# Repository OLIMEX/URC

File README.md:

# URC
Universal Remote Control soldering kit

How to transfer a command from a remote control to the Olimex URC module:

1. Enter learning mode - press and hold both buttons until red LED turns on, then release both buttons;
2. Assing a button for the new comamnd - press button 1 or button 2 until LED blinks few times then release the button; the red LED remains on;
3. Programming - point the front of the Olimex URC module to the remote control; then press and hold the command you wish to store until the red LED turns off.

## License
* License for the software is GPL3
* License for the hardware is CERN OHL v1.2
* License for the documentation is CC-BY-SA-3.0

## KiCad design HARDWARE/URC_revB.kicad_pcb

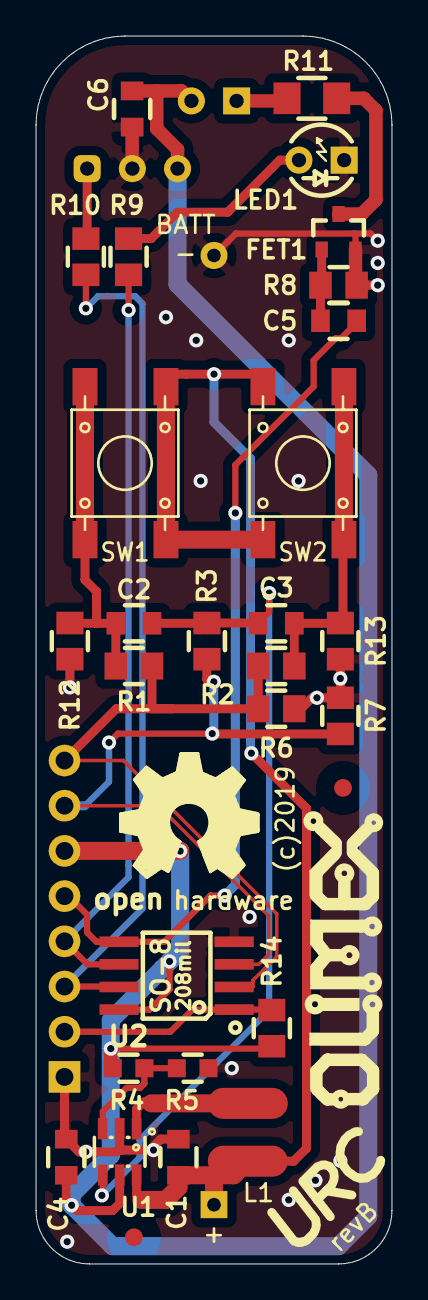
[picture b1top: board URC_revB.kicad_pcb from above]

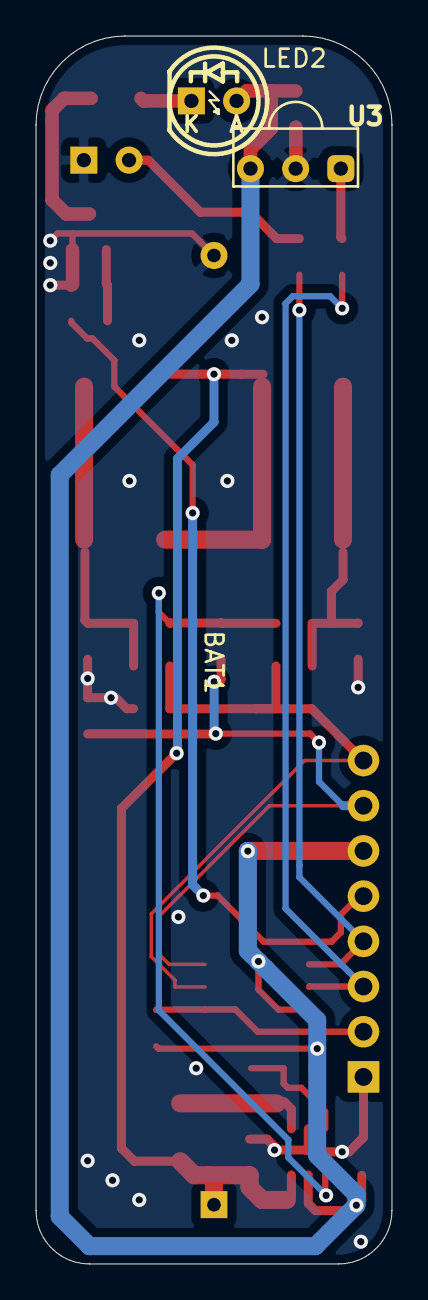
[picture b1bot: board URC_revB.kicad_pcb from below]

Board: 2 copper layers, 20.0 x 69.0 mm, 33 parts (3 on the bottom side), 19 nets.

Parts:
BAT1: Battery; BATTERY-1xAA
C1, C4, C6: 22uF; C_0805_5MIL_DWS
C2, C3, C5: 2.2uF; C_0805_5MIL_DWS
CON1: CON8; HN1x8
FET1: WNM2016-3/TR; SOT23
L1: 4.7uH; CD43
LED1: RED 3mm; LED-3mm-PTH-KA
LED2: IR333; LED-5mm-PTH-KA
R1: 22K; R_0805_5MIL_DWS
R2, R3, R6, R8: 10K; R_0805_5MIL_DWS
R4: 100K_1%; R_0603_5MIL_DWS
R5: 56.2K_1%; R_0603_5MIL_DWS
R7: 100K; R_0805_5MIL_DWS
R9, R10, R12, R13, R14: 2K; R_0805_5MIL_DWS
R11: 4.7R; R_1206_5MIL_DWS
Ref*: Val**; Fiducial1x3_transp
Ref*#2: Val**; Fiducial1x3_transp
SW1, SW2: T1107A(6x3,8x2,5MM); T1102SMD
U1: SY7080; SOT23-6
U2: ATTINY85-20PU; SO-8_208mil
U3: VS1838B; RPM7236-V

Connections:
+3V3: C4.1, C6.1, CON1.6, LED2.2, R4.1, R14.1, U1.5, U2.8, U3.3
/D_N: CON1.8, R1.2, R2.2, R6.1, U2.2
/D_P: CON1.7, R3.2, R7.2, U2.3
/MISO: CON1.4, R9.1, U2.6
/MOSI: C5.2, CON1.5, U2.5
/RESET: CON1.2, R14.2, U2.1
/SCK: CON1.3, R10.1, U2.7
GND: BAT1.2, C1.2, C4.2, C6.2, CON1.1, FET1.2, LED1.1, R5.2, R6.2, R7.1, R8.2, R12.2, R13.2, U1.2, U2.4, U3.2
unnamed: BAT1.1, C1.1, L1.1, SW1.2, SW2.1, U1.6
unnamed: C2.1, R1.1, R12.1, SW1.1
unnamed: C2.2, C3.2, R3.1, U1.4
unnamed: C3.1, R2.1, R13.1, SW2.2
unnamed: C5.1, FET1.1, R8.1
unnamed: FET1.3, R11.1
unnamed: L1.2, U1.1
unnamed: LED1.2, R9.2
unnamed: LED2.1, R11.2
unnamed: R4.2, R5.1, U1.3
unnamed: R10.2, U3.1

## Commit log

2019-06-09 initial upload
2019-06-11 update PDFs

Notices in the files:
HARDWARE/URC_revB.kicad_pcb:
(c)2019
